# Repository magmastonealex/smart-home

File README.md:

Good documentation coming soon. For now, an information dump.

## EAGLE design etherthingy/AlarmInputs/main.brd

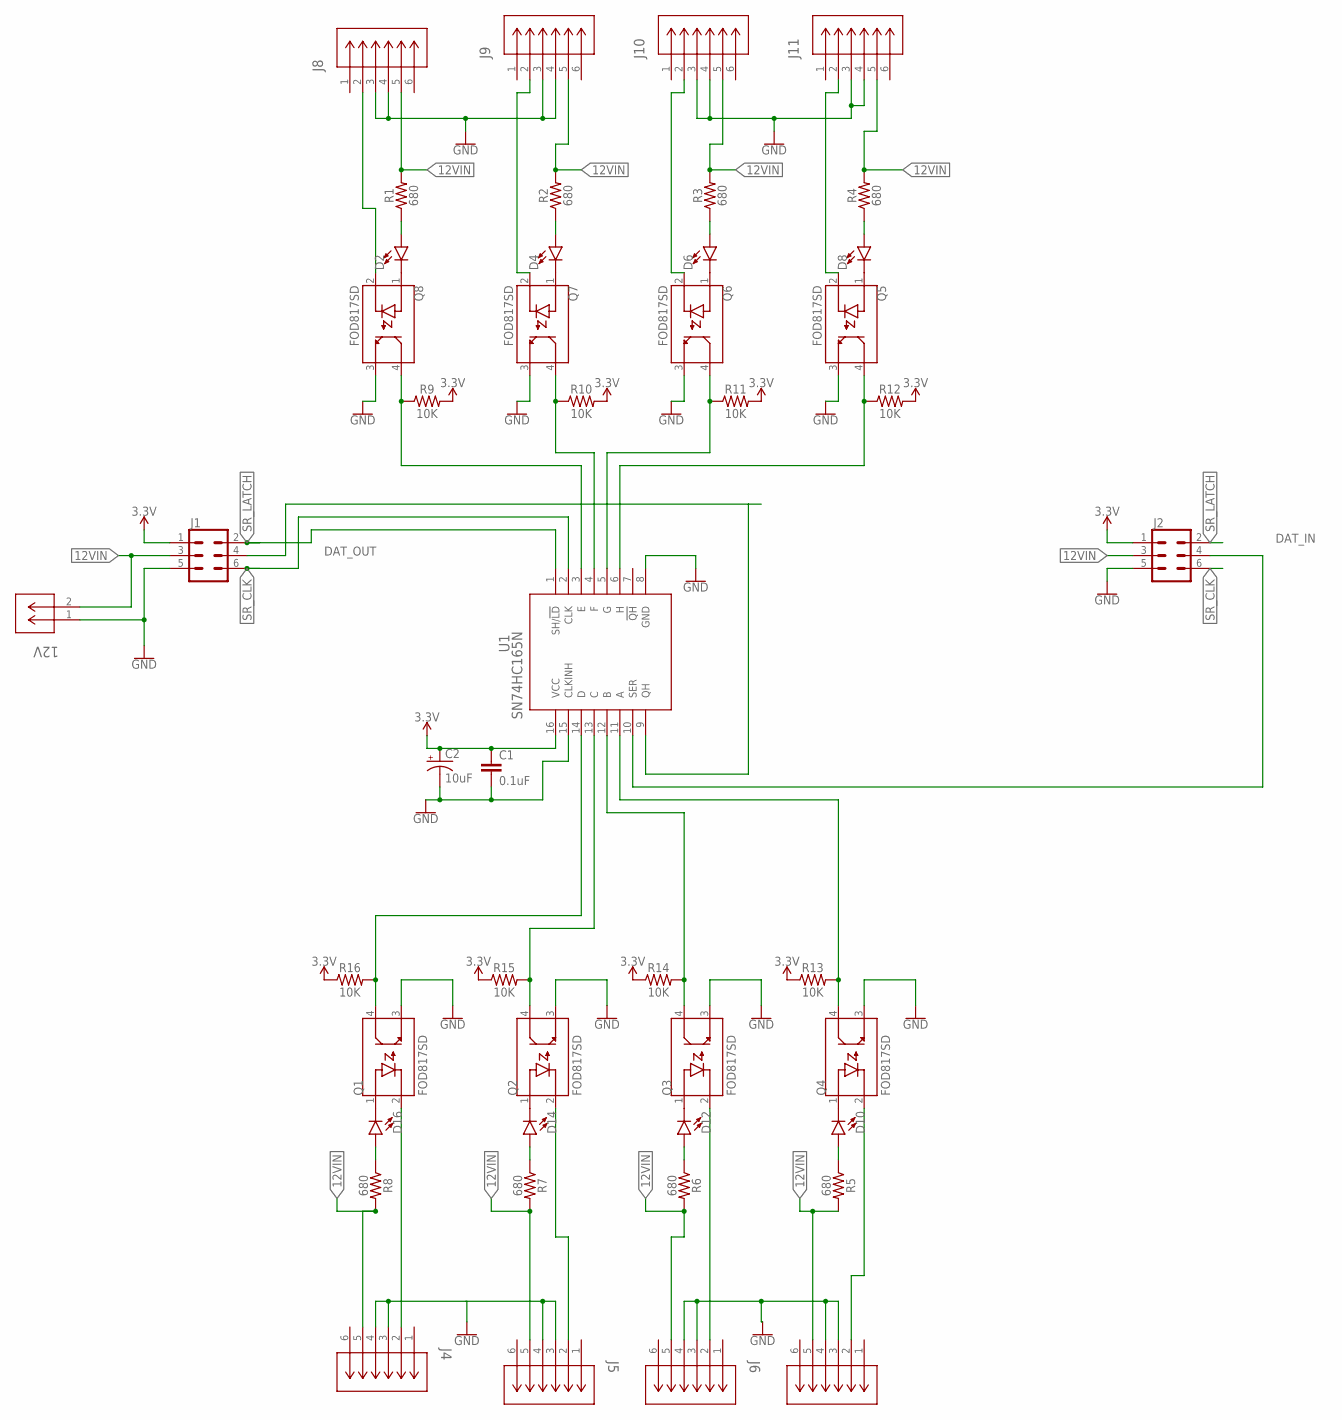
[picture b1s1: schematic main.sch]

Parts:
12V: 1725656; CONN_1725656_PXC
C1: 0.1uF; 0603
C2: 10uF; CPOL-RADIAL-2.5MM-5MM
D2, D4, D6, D8, D10, D12, D14, D16: LED0603; LED-0603
J1, J2: CONN_03X2SHROUD; 2X3-SHROUDED
J4, J5, J6, J7, J8, J9, J10, J11: E5566-Q0LK22-L; CONN6_E5566_PUL
Q1, Q2, Q3, Q4, Q5, Q6, Q7, Q8: FOD817SD; SOIC254P1016X385-4N
R1, R2, R3, R4, R5, R6, R7, R8: 680; 1206
R9, R10, R11, R12, R13, R14, R15, R16: 10K; 0603
U1: SN74HC165N; N16

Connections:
3.3V: C1.1, C2.1 (+), J1.1, J2.1, R9.2, R10.2, R11.2, R12.2, R13.1, R14.1, R15.1, R16.1, U1.16 (VCC)
12VIN: 12V.2, J1.3, J2.3, J4.5, J5.5, J6.5, J7.5, J8.5, J9.5, J10.5, J11.5, R1.2, R2.2, R3.2, R4.2, R5.2, R6.2, R7.2, R8.2
DAT_IN: J2.4, U1.10 (SER)
DAT_OUT: J1.4, U1.9 (QH)
GND: 12V.1, C1.2, C2.2 (-), J1.5, J2.5, J4.3, J4.4, J5.3, J5.4, J6.3, J6.4, J7.3, J7.4, J8.3, J8.4, J9.3, J9.4, J10.3, J10.4, J11.3, J11.4, Q1.3 (EMITTER), Q2.3 (EMITTER), Q3.3 (EMITTER), Q4.3 (EMITTER), Q5.3 (EMITTER), Q6.3 (EMITTER), Q7.3 (EMITTER), Q8.3 (EMITTER), U1.8 (GND), U1.15 (CLKINH)
unnamed: J7.2, Q4.2 (CATHODE)
unnamed: D16.C, Q1.1 (ANODE)
unnamed: D2.A, R1.1
unnamed: J6.2, Q3.2 (CATHODE)
unnamed: D14.C, Q2.1 (ANODE)
unnamed: D4.A, R2.1
unnamed: J5.2, Q2.2 (CATHODE)
unnamed: D12.C, Q3.1 (ANODE)
unnamed: D6.A, R3.1
unnamed: J4.2, Q1.2 (CATHODE)
unnamed: D10.C, Q4.1 (ANODE)
unnamed: D8.A, R4.1
unnamed: J8.2, Q8.2 (CATHODE)
unnamed: D8.C, Q5.1 (ANODE)
unnamed: D10.A, R5.1
unnamed: J9.2, Q7.2 (CATHODE)
unnamed: D6.C, Q6.1 (ANODE)
unnamed: D12.A, R6.1
unnamed: J10.2, Q6.2 (CATHODE)
unnamed: D4.C, Q7.1 (ANODE)
unnamed: D14.A, R7.1
unnamed: J11.2, Q5.2 (CATHODE)
unnamed: D2.C, Q8.1 (ANODE)
unnamed: D16.A, R8.1
unnamed: Q8.4 (COLLECTOR), R9.1, U1.3 (E)
unnamed: Q7.4 (COLLECTOR), R10.1, U1.4 (F)
unnamed: Q6.4 (COLLECTOR), R11.1, U1.5 (G)
unnamed: Q5.4 (COLLECTOR), R12.1, U1.6 (H)
unnamed: Q4.4 (COLLECTOR), R13.2, U1.11 (A)
unnamed: Q3.4 (COLLECTOR), R14.2, U1.12 (B)
unnamed: Q2.4 (COLLECTOR), R15.2, U1.13 (C)
unnamed: Q1.4 (COLLECTOR), R16.2, U1.14 (D)
SR_CLK: J1.6, J2.6, U1.2 (CLK)
SR_LATCH: J1.2, J2.2, U1.1 (SH/!LD)

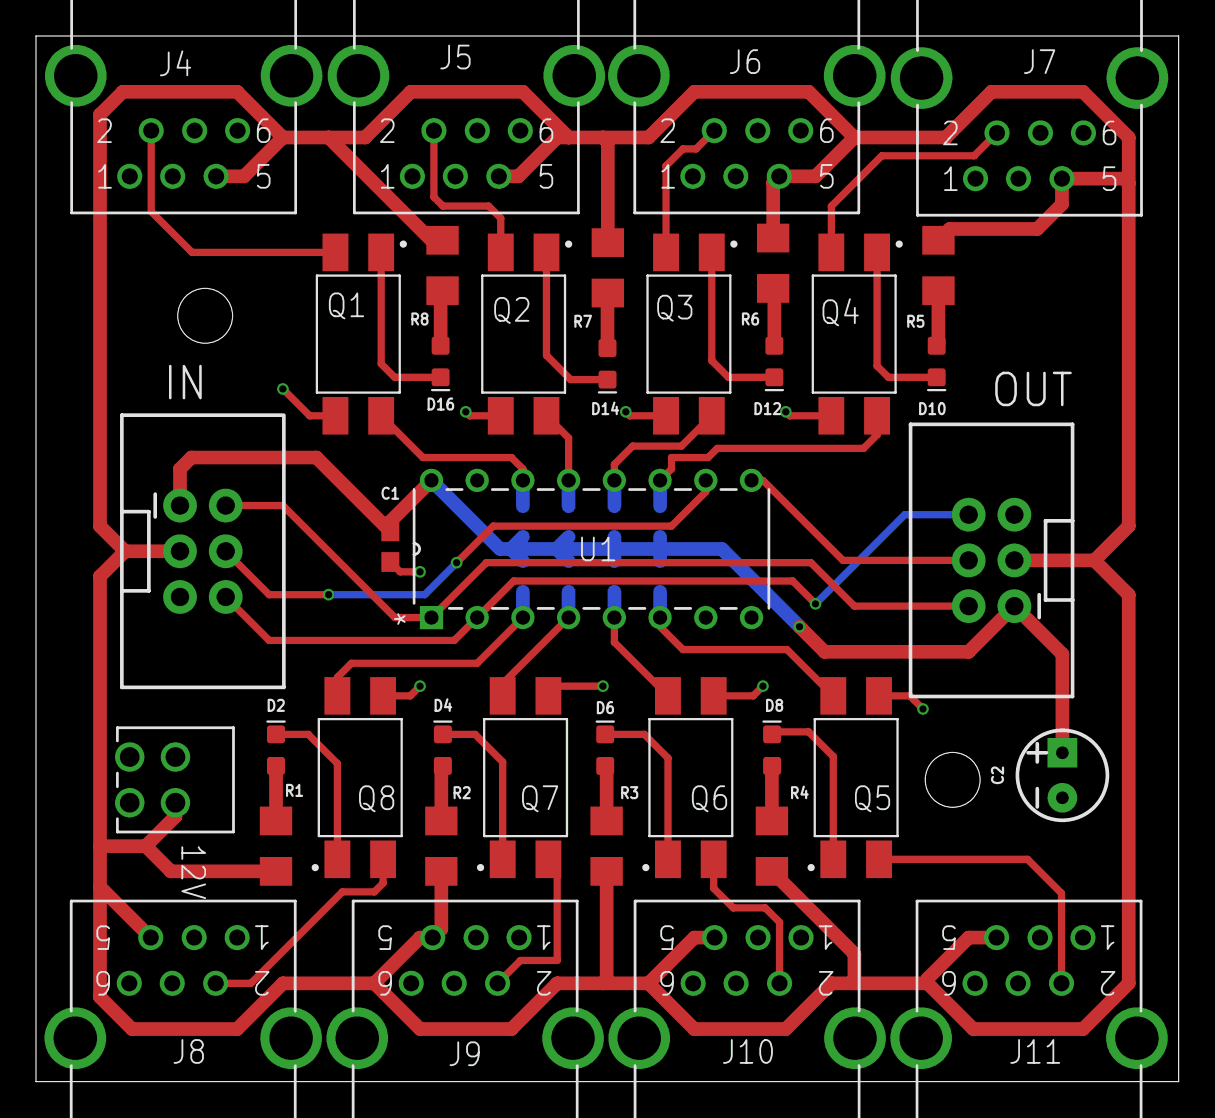
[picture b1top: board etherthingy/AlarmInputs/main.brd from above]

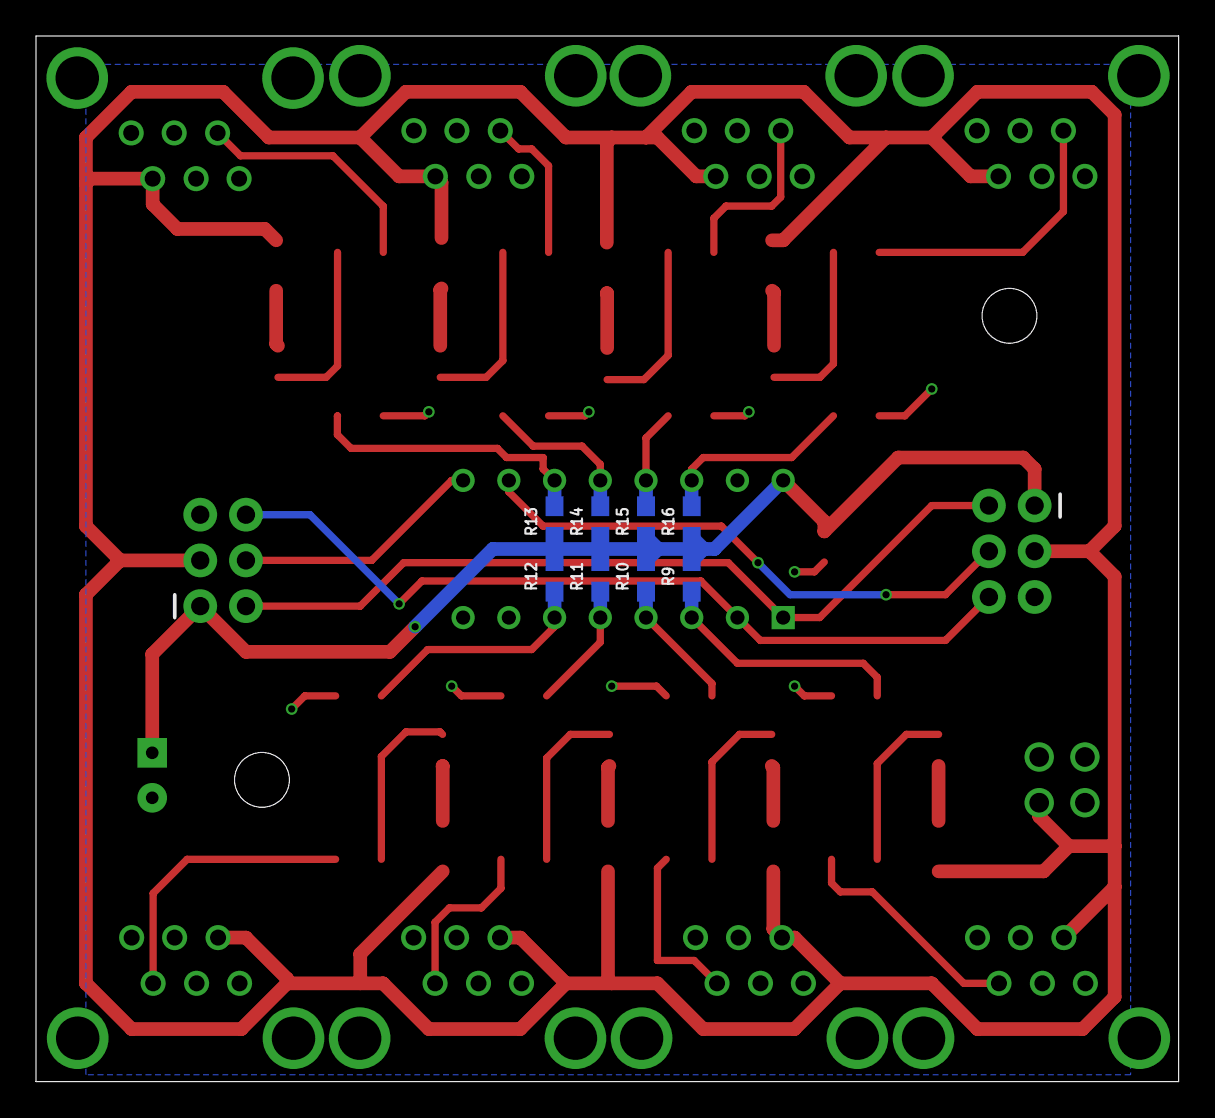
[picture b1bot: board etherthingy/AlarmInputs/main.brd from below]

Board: 2 copper layers, 63.5 x 58.1 mm, 46 parts (8 on the bottom side), 39 nets.

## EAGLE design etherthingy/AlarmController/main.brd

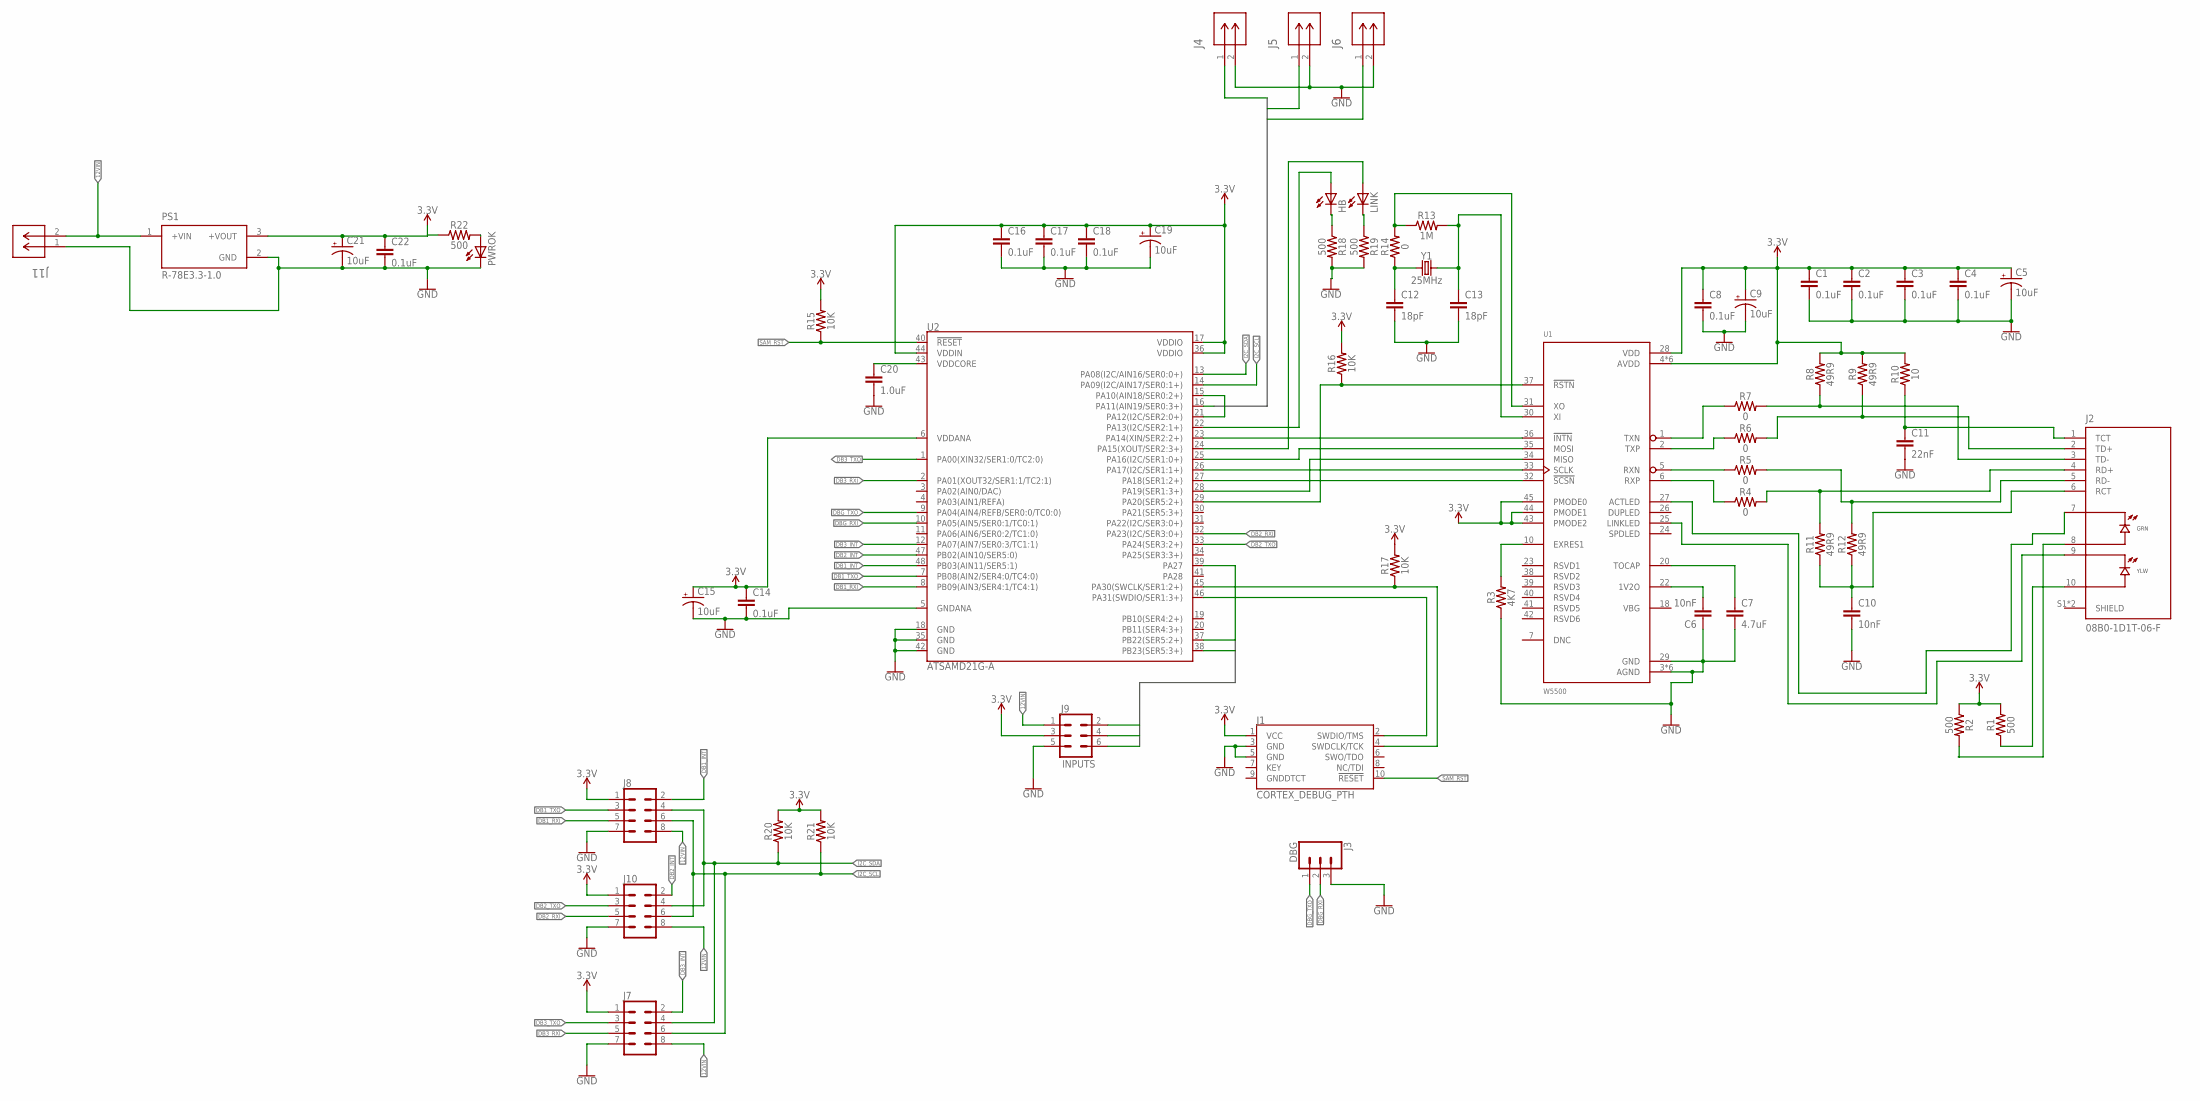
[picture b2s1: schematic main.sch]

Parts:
C1, C2, C3, C4, C8, C14, C16, C17, C18, C22: 0.1uF; 0603
C5, C9, C15, C19, C21: 10uF; CPOL-RADIAL-2.5MM-5MM
C6, C10: 10nF; 0603
C7: 4.7uF; 0603
C11: 22nF; 0603
C12, C13: 18pF; 0603
C20: 1.0uF; 0603
HB: LEDCHIPLED_0805; CHIPLED_0805
J1: CORTEX_DEBUG_PTH; 2X5-PTH-1.27MM
J2: 08B0-1D1T-06-F; BEL_08B0-1D1T-06-F
J3: DBG; 1X03_LOCK
J4: GPI1; CONN_1725656_PXC
J5: GPI2; CONN_1725656_PXC
J6: GPI3; CONN_1725656_PXC
J7, J8, J10: CONN_04X2; 2X4
J9: INPUTS; 2X3-SHROUDED
J11: 12V; CONN_1725656_PXC
LINK: LEDCHIPLED_0805; CHIPLED_0805
PS1: R-78E3.3-1.0; CONV_R-78E3.3-1.0
PWROK: LEDCHIPLED_0805; CHIPLED_0805
R1, R2, R18, R19, R22: 500; 0603
R3: 4K7; 0603
R4, R5, R6, R7, R14: 0; 0603
R8, R9, R11, R12: 49R9; 0603
R10: 10; 0603
R13: 1M; 0603
R15, R16, R17, R20, R21: 10K; 0603
U1: W5500; QFP50P900X900X160-48N
U2: ATSAMD21G-A; TQFP-48
Y1: 25MHz; HC49US

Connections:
3.3V: C1.1, C2.1, C3.1, C4.1, C5.1 (+), C8.1, C9.1 (+), C14.1, C15.1 (+), C16.1, C17.1, C18.1, C19.1 (+), C21.1 (+), C22.1, J1.1 (VCC), J7.1, J8.1, J9.3, J10.1, PS1.3 (+VOUT), R1.2, R2.1, R8.2, R9.2, R10.2, R15.2, R16.2, R17.2, R20.2, R21.2, R22.1, U1.4 (AVDD), U1.8 (AVDD), U1.11 (AVDD), U1.15 (AVDD), U1.17 (AVDD), U1.21 (AVDD), U1.28 (VDD), U1.43 (PMODE2), U1.44 (PMODE1), U1.45 (PMODE0), U2.6 (VDDANA), U2.17 (VDDIO), U2.36 (VDDIO), U2.44 (VDDIN)
12VIN: J7.8, J8.8, J9.1, J10.8, J11.2, PS1.1 (+VIN)
ACTLED: J2.7, U1.27 (ACTLED)
DB1_INT: J8.2, U2.48 (PB03(AIN11/SER5:1))
DB1_RXI: J8.5, U2.8 (PB09(AIN3/SER4:1/TC4:1))
DB1_TXO: J8.3, U2.7 (PB08(AIN2/SER4:0/TC4:0))
DB2_INT: J10.2, U2.47 (PB02(AIN10/SER5:0))
DB2_RXI: J10.5, U2.32 (PA23(I2C/SER3:0+))
DB2_TXO: J10.3, U2.33 (PA24(SER3:2+))
DB3_INT: J7.2, U2.12 (PA07(AIN7/SER0:3/TC1:1))
DB3_RXI: J7.5, U2.2 (PA01(XOUT32/SER1:1/TC2:1))
DB3_TXO: J7.3, U2.1 (PA00(XIN32/SER1:0/TC2:0))
DBG_RXI: J3.2, U2.10 (PA05(AIN5/SER0:1/TC0:1))
DBG_TXO: J3.1, U2.9 (PA04(AIN4/REFB/SER0:0/TC0:0))
GND: C1.2, C2.2, C3.2, C4.2, C5.2 (-), C6.1, C7.2, C8.2, C9.2 (-), C10.2, C11.2, C12.2, C13.2, C14.2, C15.2 (-), C16.2, C17.2, C18.2, C19.2 (-), C20.2, C21.2 (-), C22.2, J1.3 (GND), J1.5 (GND), J3.3, J4.2, J5.2, J6.2, J7.7, J8.7, J9.5, J10.7, J11.1, PS1.2 (GND), PWROK.C, R3.1, R18.2, R19.2, U1.3 (AGND), U1.9 (AGND), U1.14 (AGND), U1.16 (AGND), U1.19 (AGND), U1.29 (GND), U1.48 (AGND), U2.5 (GNDANA), U2.18 (GND), U2.35 (GND), U2.42 (GND)
GPI1: J4.1, U2.15 (PA10(AIN18/SER0:2+))
GPI2: J5.1, U2.16 (PA11(AIN19/SER0:3+))
GPI3: J6.1, U2.21 (PA12(I2C/SER2:0+))
I2C_SCL: J7.6, J8.6, J10.6, R21.1, U2.14 (PA09(I2C/AIN17/SER0:1+))
I2C_SDA: J7.4, J8.4, J10.4, R20.1, U2.13 (PA08(I2C/AIN16/SER0:0+))
INTR: U1.36 (!INTN), U2.23 (PA14(XIN/SER2:2+))
MISO: U1.34 (MISO), U2.28 (PA19(SER1:3+))
MOSI: U1.35 (MOSI), U2.25 (PA16(I2C/SER1:0+))
unnamed: J1.4 (SWDCLK/TCK), R17.1, U2.45 (PA30(SWCLK/SER1:2+))
unnamed: J1.2 (SWDIO/TMS), U2.46 (PA31(SWDIO/SER1:3+))
unnamed: PWROK.A, R22.2
unnamed: J2.10, R1.1
unnamed: J2.8, R2.2
unnamed: C6.2, U1.22 (1V2O)
unnamed: C7.1, U1.20 (TOCAP)
unnamed: R3.2, U1.10 (EXRES1)
unnamed: C12.1, R14.1, Y1.1
unnamed: C11.1, J2.1 (TCT), R10.1
unnamed: HB.A, U2.22 (PA13(I2C/SER2:1+))
unnamed: HB.C, R18.1
unnamed: C20.1, U2.43 (VDDCORE)
unnamed: LINK.A, U2.24 (PA15(XOUT/SER2:3+))
unnamed: LINK.C, R19.1
PHYLINK: J2.9, U1.25 (LINKLED)
PHYRST: R16.1, U1.37 (!RSTN), U2.29 (PA20(SER5:2+))
RCT_GND: C10.1, J2.6 (RCT), R11.1, R12.1
RXP_N: R5.1, U1.5 (RXN)
RXP_P: R4.1, U1.6 (RXP)
RX_N: J2.5 (RD-), R5.2, R12.2
RX_P: J2.4 (RD+), R4.2, R11.2
SAM_RST: J1.10 (!RESET), R15.1, U2.40 (!RESET!)
SCLK: U1.33 (SCLK), U2.26 (PA17(I2C/SER1:1+))
SPI_SS: U1.32 (!SCSN), U2.27 (PA18(SER1:2+))
SR_CLK: J9.6, U2.39 (PA27)
SR_DAT: J9.4, U2.38 (PB23(SER5:3+))
SR_LATCH: J9.2, U2.37 (PB22(SER5:2+))
TXP_N: R7.1, U1.1 (TXN)
TXP_P: R6.1, U1.2 (TXP)
TX_N: J2.3 (TD-), R7.2, R8.1
TX_P: J2.2 (TD+), R6.2, R9.1
XO_N: R13.1, R14.2, U1.31 (XO)
XO_P: C13.1, R13.2, U1.30 (XI), Y1.2

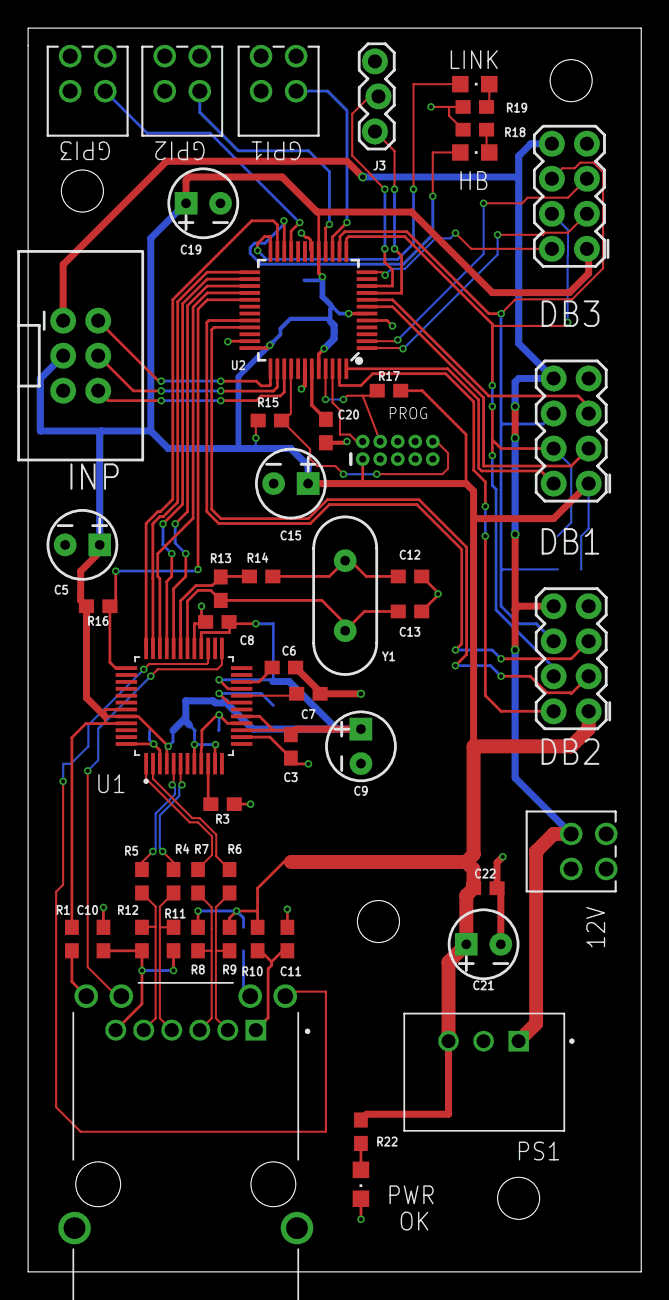
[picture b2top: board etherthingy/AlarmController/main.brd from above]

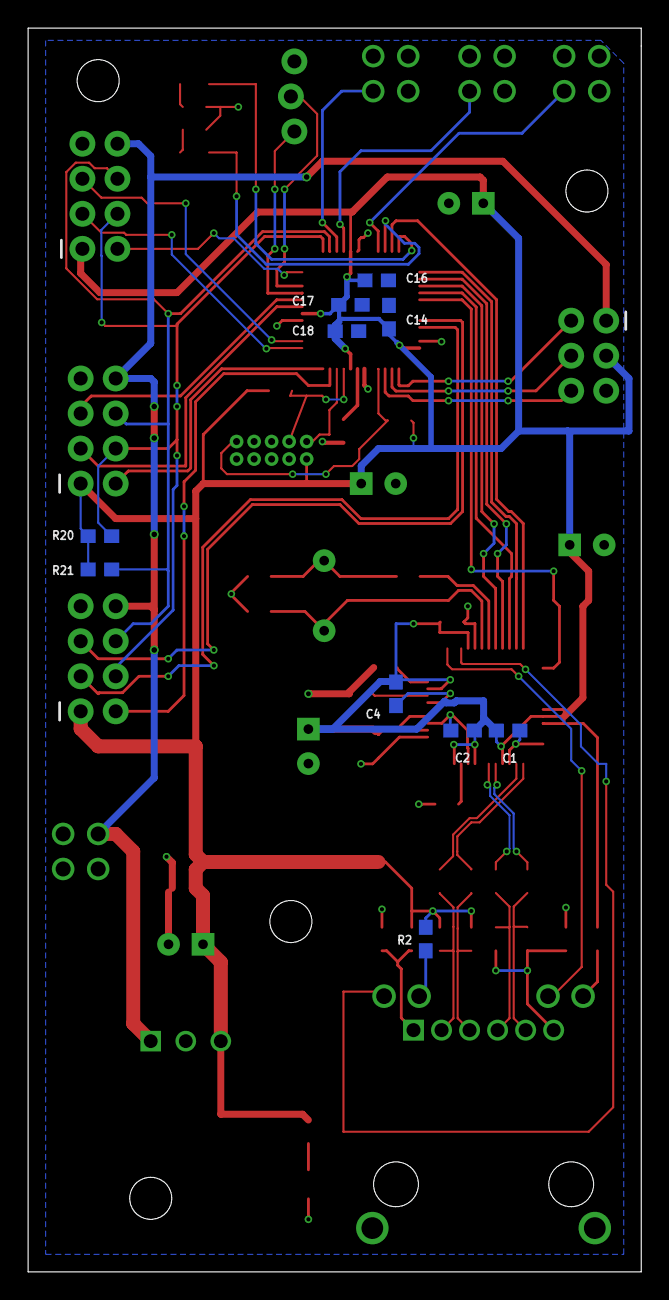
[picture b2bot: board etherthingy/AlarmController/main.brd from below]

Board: 2 copper layers, 44.5 x 90.2 mm, 62 parts (10 on the bottom side), 57 nets.

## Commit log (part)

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2019-04-13 Initial commit, some pics plus curtain plus kindlepanel
2019-08-21 Initial HA commit
2019-08-22 Volume adjust on TV input change
2019-08-30 Don't close curtain until sun has actually set
2019-10-07 Update alarm for a more graceful wake-up
2019-10-13 Add roomba virtual wall info
2019-11-13 Add christmas lights to groups and main panel.
2019-11-19 Update config for dht22 + holiday lights
2019-11-26 Front door open last updated
2019-12-26 Add Google Assistant config, remove unifi device tracker (set up in HA UI now)
2019-12-26 Add some more scenes to make google assistant nicer to use
2020-01-01 Start describing OTA
2020-01-01 add processing files
2020-01-01 Add MQTT cacher, video looper, lightbutton, frontdoor
2020-01-01 update frontdoor readme with picture
2020-01-03 volume level working properly. It's decimal from 0 to 1
2020-01-08 Add process.py
2020-01-09 update py
2020-01-10 start adding tests to process_lib
2020-01-10 Remove unneeded muxdelay
2020-01-10 Dockerize OTA postprocessing
2020-01-10 Update some ota stuff now that it's actually deployed
2020-02-12 Update kindlepanel with upcoming events field
2020-02-12 Configuration for input_boolean and new guest vlan
2020-02-12 Add calendarfetcher to update calendar input_text for kindle
2020-02-20 Handle empty event string a bit better. Look exactly 7 days ahead.
2020-05-09 New apartment, new HA config. Pre lovelace swap.
2020-05-09 Commit Pioneer controller application
2020-05-09 Lovelace UI, attempt at getting circleci to check HA config
2020-05-09 circleci config tweak
2020-05-09 Add fake service account to try and get config tests to pass
2020-05-09 add some apt packages
2020-05-09 Add roomba & front door sensor
2020-05-12 Add samsung tv
2020-05-12 Finally commit tizenapi, remove old tizen stuff from config.yaml
2020-05-12 new tv config
2020-05-12 Oops. Revoke api key
2020-05-12 Update bind address
2020-05-12 Add port
2020-05-12 grr forgot quote
2020-05-12 config update test
2020-05-19 Add Yamaha receiver
2020-05-19 cache ha deps?
2020-05-19 Update living room universal tv
2020-05-20 Bump httplib2 from 0.17.0 to 0.18.0 in /calendarfetcher
    Bumps [httplib2](https://github.com/httplib2/httplib2) from 0.17.0 to 0.18.0.
    - [Release notes](https://github.com/httplib2/httplib2/releases)
    - [Changelog](https://github.com/httplib2/httplib2/blob/master/CHANGELOG)
    - [Commits](https://github.com/httplib2/httplib2/compare/v0.17.0...v0.18.0)
2020-10-16 Add OpenCV code to detect deadbolt state
2020-10-16 Misc updates
2020-10-17 Swap over to perspective transform, dockerize in prep for deployment
2020-11-21 Add christmas lights
2020-12-04 Finish schematic for main board, starting routing
2020-12-04 Add PWROK led. Routing continues.
2020-12-04 more routing
2020-12-04 more routing & layout
2020-12-04 Routing continues
2020-12-05 Routing complete
2020-12-05 Re-routing to add DB3 port
2020-12-05 Adjust isolate of ground pour, move 12V header, add asfv4 starter
2020-12-05 Re-labelling
2020-12-05 Labelling, moving, cleanup
2020-12-12 Inputs board complete
2020-12-14 Use barrier strips instead of RJ11
2020-12-20 Going back to RJ11s
2021-02-08 Bump httplib2 from 0.18.0 to 0.19.0 in /calendarfetcher
    Bumps [httplib2](https://github.com/httplib2/httplib2) from 0.18.0 to 0.19.0.
    - [Release notes](https://github.com/httplib2/httplib2/releases)
    - [Changelog](https://github.com/httplib2/httplib2/blob/master/CHANGELOG)
    - [Commits](https://github.com/httplib2/httplib2/compare/v0.18.0...v0.19.0)
2021-03-20 Bump jinja2 from 2.11.2 to 2.11.3 in /tizenapi
    Bumps [jinja2](https://github.com/pallets/jinja) from 2.11.2 to 2.11.3.
    - [Release notes](https://github.com/pallets/jinja/releases)
    - [Changelog](https://github.com/pallets/jinja/blob/master/CHANGES.rst)
    - [Commits](https://github.com/pallets/jinja/compare/2.11.2...2.11.3)
2021-04-26 Early-commit for receipt-parser
2021-07-27 Start on e-ink server
2021-08-02 Rough widget-ization in progress
2021-08-08 Calendar becomes a widget
2021-09-04 rework doorlocked for garage door status detection
2021-09-11 Add rough sketch of EVL-4 plans
2021-09-11 Fix markdownification
2021-09-12 Working interface to UNO-8 module
2021-09-14 esp8266 implementation for UNO-8. Last step before FW bringup begins
2021-09-14 Add debug serial support. Next step is to flash & see if it works.
2021-09-14 First firmware flashed on evl-4
2021-09-15 NIC initialization in progress. I'm able to talk to it.
2021-09-15 PHY works to send and receive packets! Need to tidy driver code
2021-09-15 Reorg NIC code, start prototyping structures for IP stack
2021-09-16 timer config to enable ARP
2021-09-16 Beginning IP stack implementation. ARP implemented.
2021-09-16 netstack: Remove excess debugging to get ARP responses just under 1ms
2021-09-17 IP packet parsing mostly working
2021-09-17 Add ICMP/UDP support. IP stack complete
2021-09-18 CoAP packetization complete
2021-09-18 CoAP router in place, ready to start on pubsub
2021-09-18 rough sketch of sensor publish implementation
2021-09-18 Bad CoAP broker implementation. FW on the board seems to be working well.
2021-09-19 IT WORKS! The whole application is functional. Still have EEPROM read/write to do, and a WDT. Something is misbheaving in go-coap, so deleted a middleware to see if it helps.
2021-09-19 Config persistence, safety WDT. Some ideas to fix the strange fake-ack from go-coap
2021-09-19 README updates to indicate current state.
2021-09-19 Implement broker in Node, where there seems to be a solid CoAP client
2021-09-19 Update broker for proper response code, confirm not double-acking
2021-09-19 README updates to reflect current state
2021-09-19 Add Docker config for coapbroker
2021-09-19 fix busted ARP which was always broadcasting. Back off on watchdog agressiveness
2021-09-19 fix CoAP: Start with a random message ID.
2021-10-04 Add bad implementation for ics fetching
2021-10-04 Config file loading
2021-10-15 Update einkdisplay client to use platformio for build/deploy
2021-10-15 Updates for real deployment
2021-10-15 fix gitignore
2021-11-05 Network Diagrams
2022-02-25 Initial Ansible work to provision cluster - working off VMs for now.
2022-02-26 Setup gluster, start writing some jobs
2022-02-26 Initial support work for anycast. Need to make actual docker container for BIRD, but otherwise functional
2022-02-27 Anycast sidecar built and ready to go.
2022-02-27 Anycast fully functional - configured Traefik & pihole to use. Set up demo app demonstrating traefik. Vault, then TLS for Traefik up next.
2022-02-27 Servers receive TLS certificates, Consul & Nomad ACLs are in place. Ready to bring up Vault
2022-02-27 Vault can be brought up in the cluster with Nomad integration.
2022-02-27 Unseal playbook, demonstrate secret fetching. Need to hook Traefik up to ACME, then good to go.
2022-03-04 Prove connect service mesh is functional. Next up set up Vault CA.
2022-03-05 Connect set up with Vault PKI. Kinda sorta working with Traefik, broken because of Vagrant silliness
2022-03-05 Traefik + Connect mesh working.
2022-03-05 working without exposing any ports to network
2022-03-05 Organize Ansible files. Preparing for fresh deployment
2022-03-05 Re-organize Ansible with ordering
2022-03-05 Better deployment instructions
2022-03-05 Clarified deploy instructions
2022-03-08 Update from real cluster deployment - add Anycast support through Wireguard
2022-03-13 Add support for dynamic MySQL databases per-app, including automated backups
2022-03-14 Deploy Conduit and Gitea to the cluster
2022-03-30 Bump minimist from 1.2.5 to 1.2.6 in /evl4-cfw/broker-node/app
    Bumps [minimist](https://github.com/substack/minimist) from 1.2.5 to 1.2.6.
    - [Release notes](https://github.com/substack/minimist/releases)
    - [Commits](https://github.com/substack/minimist/compare/1.2.5...1.2.6)
    ---
    updated-dependencies:
    - dependency-name: minimist
2022-04-28 Add Ansible stuff for backnas
2022-04-28 Infrastructure updates with the real cluster - use postgres and patroni instead of mysql on gluster (too slow)
2022-05-16 Bump async from 3.2.1 to 3.2.3 in /evl4-cfw/broker-node/app
    Bumps [async](https://github.com/caolan/async) from 3.2.1 to 3.2.3.
    - [Release notes](https://github.com/caolan/async/releases)
    - [Changelog](https://github.com/caolan/async/blob/master/CHANGELOG.md)
    - [Commits](https://github.com/caolan/async/compare/v3.2.1...v3.2.3)
    ---
    updated-dependencies:
2022-05-16 Bump urllib3 from 1.25.9 to 1.26.5 in /tizenapi
    Bumps [urllib3](https://github.com/urllib3/urllib3) from 1.25.9 to 1.26.5.
    - [Release notes](https://github.com/urllib3/urllib3/releases)
    - [Changelog](https://github.com/urllib3/urllib3/blob/main/CHANGES.rst)
    - [Commits](https://github.com/urllib3/urllib3/compare/1.25.9...1.26.5)
    ---
    updated-dependencies:
2022-05-16 Bump urllib3 from 1.25.8 to 1.26.5 in /calendarfetcher
    Bumps [urllib3](https://github.com/urllib3/urllib3) from 1.25.8 to 1.26.5.
    - [Release notes](https://github.com/urllib3/urllib3/releases)
    - [Changelog](https://github.com/urllib3/urllib3/blob/main/CHANGES.rst)
    - [Commits](https://github.com/urllib3/urllib3/compare/1.25.8...1.26.5)
    ---
    updated-dependencies:
2022-11-12 Bump minimatch from 3.0.4 to 3.1.2 in /evl4-cfw/broker-node/app
    Bumps [minimatch](https://github.com/isaacs/minimatch) from 3.0.4 to 3.1.2.
    - [Release notes](https://github.com/isaacs/minimatch/releases)
    - [Commits](https://github.com/isaacs/minimatch/compare/v3.0.4...v3.1.2)
    ---
    updated-dependencies:
    - dependency-name: minimatch
2022-12-08 Bump certifi from 2019.11.28 to 2022.12.7 in /calendarfetcher
    Bumps [certifi](https://github.com/certifi/python-certifi) from 2019.11.28 to 2022.12.7.
    - [Release notes](https://github.com/certifi/python-certifi/releases)
    - [Commits](https://github.com/certifi/python-certifi/compare/2019.11.28...2022.12.07)
    ---
    updated-dependencies:
    - dependency-name: certifi
2023-02-16 Bump werkzeug from 1.0.1 to 2.2.3 in /tizenapi
    Bumps [werkzeug](https://github.com/pallets/werkzeug) from 1.0.1 to 2.2.3.
    - [Release notes](https://github.com/pallets/werkzeug/releases)
    - [Changelog](https://github.com/pallets/werkzeug/blob/main/CHANGES.rst)
    - [Commits](https://github.com/pallets/werkzeug/compare/1.0.1...2.2.3)
    ---
    updated-dependencies:
2023-02-24 Bump golang.org/x/net in /mqtt_cacher
    Bumps [golang.org/x/net](https://github.com/golang/net) from 0.0.0-20191119073136-fc4aabc6c914 to 0.7.0.
    - [Release notes](https://github.com/golang/net/releases)
    - [Commits](https://github.com/golang/net/commits/v0.7.0)
    ---
    updated-dependencies:
    - dependency-name: golang.org/x/net
2023-02-24 Bump golang.org/x/net in /videolooper
    Bumps [golang.org/x/net](https://github.com/golang/net) from 0.0.0-20191119073136-fc4aabc6c914 to 0.7.0.
    - [Release notes](https://github.com/golang/net/releases)
    - [Commits](https://github.com/golang/net/commits/v0.7.0)
    ---
    updated-dependencies:
    - dependency-name: golang.org/x/net
2023-02-25 Bump golang.org/x/net in /piocmd
    Bumps [golang.org/x/net](https://github.com/golang/net) from 0.0.0-20200324143707-d3edc9973b7e to 0.7.0.
    - [Release notes](https://github.com/golang/net/releases)
    - [Commits](https://github.com/golang/net/commits/v0.7.0)
    ---
    updated-dependencies:
    - dependency-name: golang.org/x/net

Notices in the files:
parts and their libraries:
SparkFun-Capacitors: Licensing: Creative Commons ShareAlike 4.0 International - https://creativecommons.org/licenses/by-sa/4.0
COPYRIGHT: Copyright (C) 2018 Accelerated Designs. All rights reserved
COPYRIGHT: Copyright (C) 2016 Accelerated Designs. All rights reserved
